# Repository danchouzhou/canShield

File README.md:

# canShield
CAN Transceiver shield for NuMaker-Volcano<br>
You can order the board here!!<br>
https://oshpark.com/shared_projects/PI9Q1T6t

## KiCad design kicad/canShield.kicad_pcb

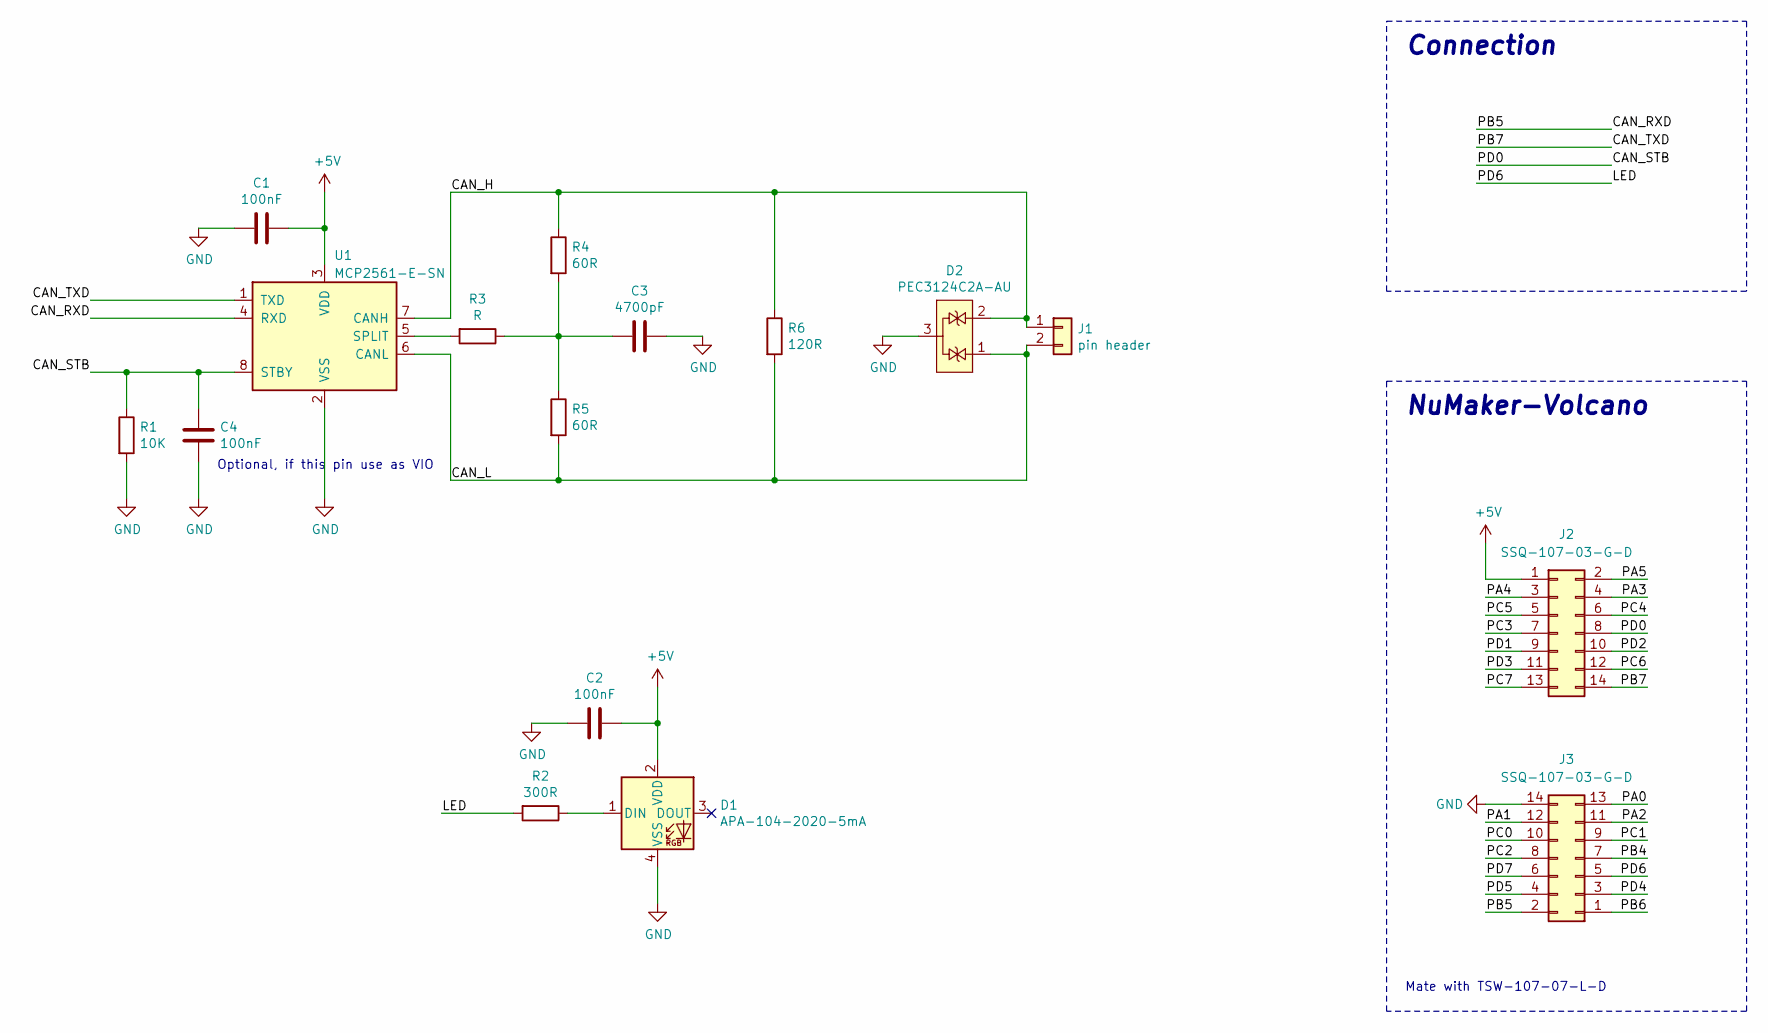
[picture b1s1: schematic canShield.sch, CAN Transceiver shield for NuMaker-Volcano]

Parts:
C1, C2, C4: 100nF; C_0603_1608Metric
C3: 4700pF; C_0603_1608Metric
D1: APA-104-2020-5mA
D2: PEC3124C2A-AU; SOT-23; Manufacturer P/N PEC3124C2A-AU_R1_000A1
J1: pin header; PinHeader_1x02_P2.54mm_Vertical
J2, J3: SSQ-107-03-G-D; PinSocket_2x07_P2.54mm_Vertical
R1: 10K; R_0603_1608Metric
R2: 300R; R_0603_1608Metric
R3: R; R_0603_1608Metric
R4, R5: 60R; R_0805_2012Metric
R6: 120R; R_Axial_DIN0207_L6.3mm_D2.5mm_P10.16mm_Horizontal
U1: MCP2561-E-SN; SOIC-8_3.9x4.9mm_P1.27mm

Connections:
+5V: C1.1, C2.1, D1.2 (VDD), J2.1, U1.3 (VDD)
/CAN_H: D2.2, J1.1, R4.1, R6.1, U1.7 (CANH)
/CAN_L: D2.1, J1.2, R5.2, R6.2, U1.6 (CANL)
/CAN_RXD: J3.2, U1.4 (RXD)
/CAN_STB: C4.1, J2.8, R1.1, U1.8 (STBY)
/CAN_TXD: J2.14, U1.1 (TXD)
/LED: J3.5, R2.2
/PA0: J3.13
/PA1: J3.12
/PA2: J3.11
/PA3: J2.4
/PA4: J2.3
/PA5: J2.2
/PB4: J3.7
/PB6: J3.1
/PC0: J3.10
/PC1: J3.9
/PC2: J3.8
/PC3: J2.7
/PC4: J2.6
/PC5: J2.5
/PC6: J2.12
/PC7: J2.13
/PD1: J2.9
/PD2: J2.10
/PD3: J2.11
/PD4: J3.3
/PD5: J3.4
/PD7: J3.6
GND: C1.2, C2.2, C3.1, C4.2, D1.4 (VSS), D2.3, J3.14, R1.2, U1.2 (VSS)
unnamed: C3.2, R3.1, R4.2, R5.1
unnamed: D1.1 (DIN), R2.1
unnamed: R3.2, U1.5 (SPLIT)

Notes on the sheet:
Connection
NuMaker-Volcano
Mate with TSW-107-07-L-D
Optional, if this pin use as VIO

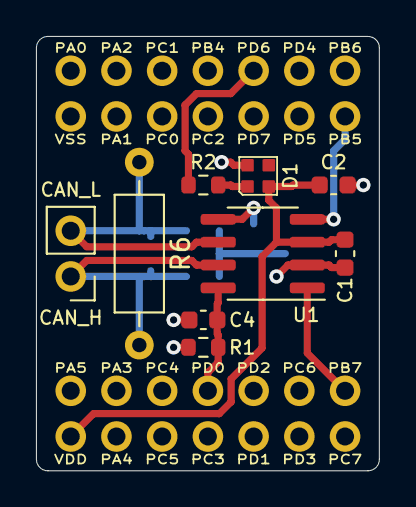
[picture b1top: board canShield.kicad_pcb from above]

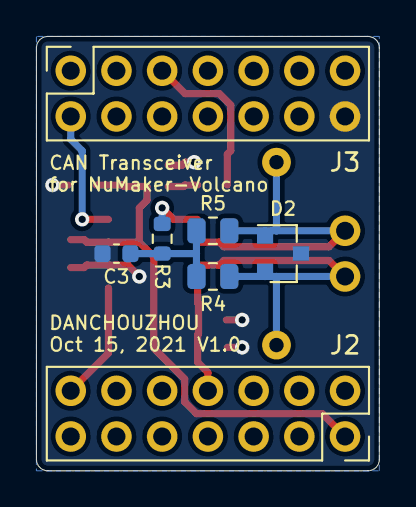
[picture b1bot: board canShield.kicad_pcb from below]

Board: 2 copper layers, 19.1 x 24.1 mm, 16 parts (7 on the bottom side), 11 nets.

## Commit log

2021-10-15 Add KiCad files
2021-10-18 Add submodule
2021-10-18 Update copyright
2021-10-18 Remove submodule
2021-11-08 Add NeoPixel
2021-11-09 Add CAN_NormalMode_Rx
2021-11-09 Add support for different type of transceiver
2022-08-03 Move to library
2022-08-03 Update pin mode resolving method
2022-08-03 Update gpio base resolving method
2022-08-03 Update license
2022-08-03 Add NuLibrary
2022-08-03 Update submodule path
2022-08-03 Add NuLibrary submodule
2022-08-03 Remove library
2022-08-03 Remove user library
2022-08-03 Use NuLibrary submodule
2022-08-03 Update submodule
